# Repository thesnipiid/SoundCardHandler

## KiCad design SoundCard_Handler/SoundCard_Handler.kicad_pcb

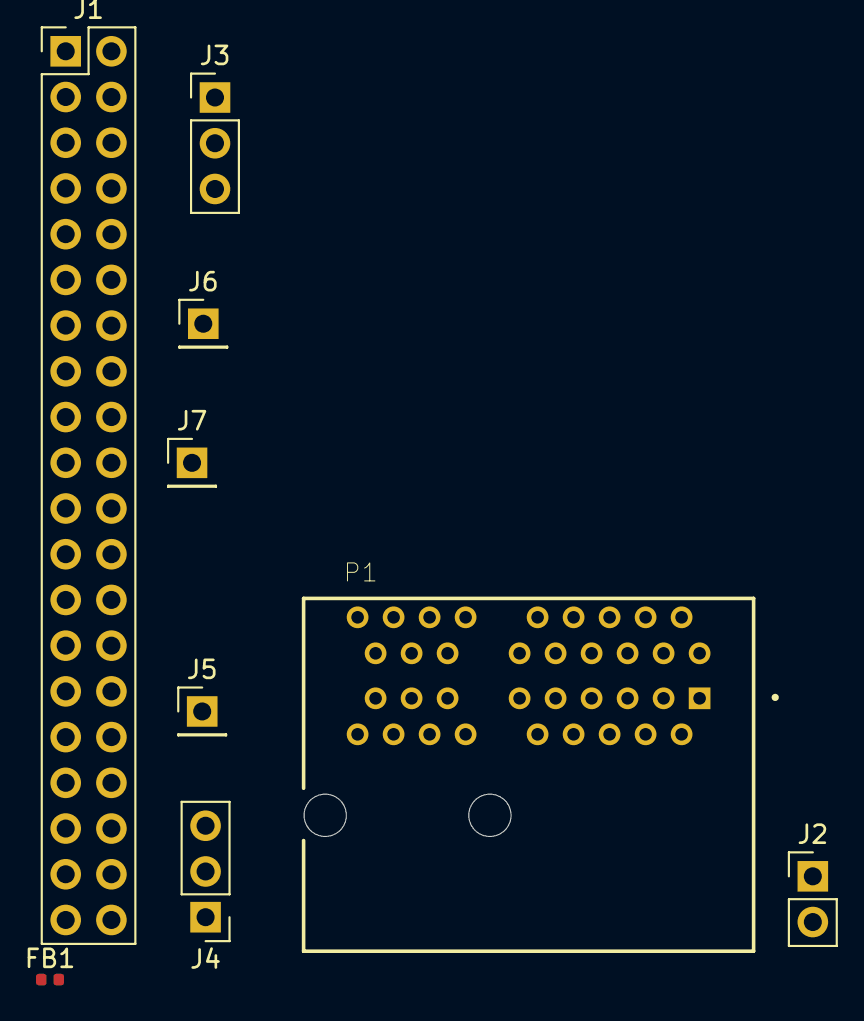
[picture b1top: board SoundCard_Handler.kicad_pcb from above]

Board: 2 copper layers, 9 parts (0 on the bottom side), 13 nets, no tracks yet.

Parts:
FB1: Ferrite_Bead; C_0402_1005Metric
J1: Raspberry_Pi_2_3; PinHeader_2x20_P2.54mm_Vertical
J2: Conn_01x02_Male; PinHeader_1x02_P2.54mm_Vertical
J3, J4: Conn_01x03_Male; PinHeader_1x03_P2.54mm_Vertical
J5, J6, J7: Conn_01x01_Male; PinHeader_1x01_P2.54mm_Vertical
P1: CONN_36_P1.00_PCI; SAMTEC_PCIE-036-02-X-D-RA

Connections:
+24V: P1.A16, P1.A17, P1.A18
/ATT_CLOCK: J1.40, J4.1, P1.A1
/ATT_DATA_IN: J1.38, J4.3, P1.A3
/ATT_~CS~: J1.24, J4.2, P1.A2
/BCLK: J6.1, P1.B8
/FSYNC: J7.1, P1.B11
/SCL: J1.5, J3.2, P1.A10
/SDA: J1.3, J3.1, P1.A9
/SDOUT: J5.1, P1.B5
/SHDNZ: J3.3, P1.A11
GND: J1.6, J1.9, J1.14, J1.20, J1.25, J1.30, J1.34, J1.39, P1.A4, P1.A5, P1.A7, P1.A8, P1.A12, P1.A13, P1.A14, P1.A15, P1.B1, P1.B2, P1.B3, P1.B4, P1.B6, P1.B7, P1.B9, P1.B10, P1.B15, P1.B16, P1.B17, P1.B18
unnamed: FB1.1, P1.B12, P1.B13, P1.B14
VCC: FB1.2, J1.2, J1.4, J2.2

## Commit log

2020-08-04 init
